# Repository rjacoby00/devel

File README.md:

# Devel
### Ryan Jacoby

This is a repository full of random bits of code I have written for various assingments, projects, and classes over time.  Some of the code I am not allowed to share and has been omited due to it being private, a homework solution, copyrighted code that I cannot distribute, or secret/classified information.  If you have any questions or need to see something that you think might have been redacted, feel free to email me at [rjacoby00@icloud.com](mailto:rjacoby00@icloud.com).

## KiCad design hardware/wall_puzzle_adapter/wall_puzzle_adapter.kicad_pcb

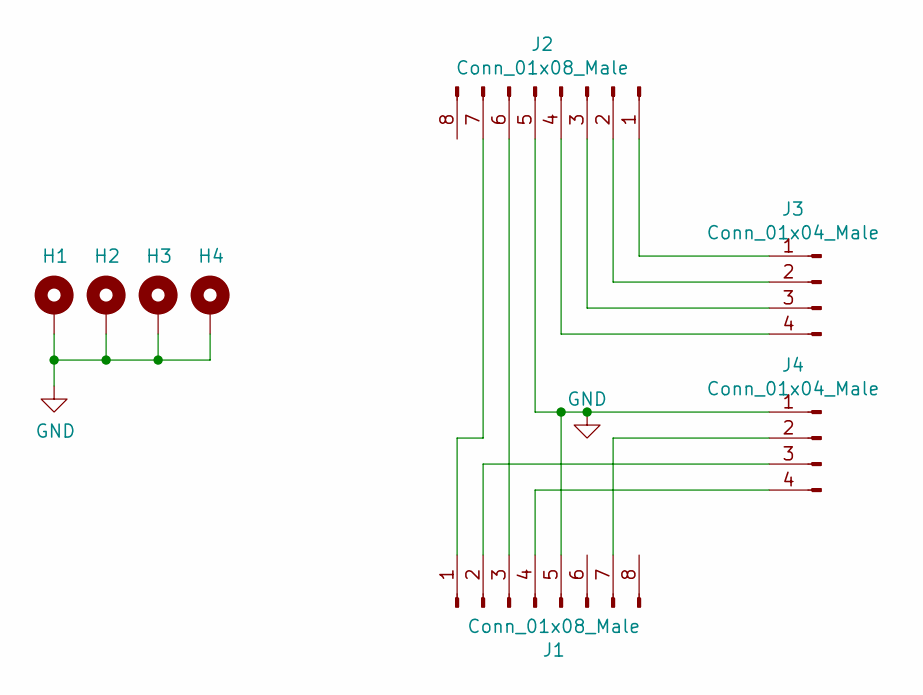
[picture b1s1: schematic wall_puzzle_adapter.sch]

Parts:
H1, H2, H3, H4: MountingHole_Pad; MountingHole_4mm_Pad_Via
J1: Conn_01x08_Male; RJ45_Amphenol_54602-x08_Horizontal
J2: Conn_01x08_Male; JST_XH_S8B-XH-A_1x08_P2.50mm_Horizontal
J3, J4: Conn_01x04_Male; TerminalBlock_Altech_AK300-4_P5.00mm

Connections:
GND: H1.1, H2.1, H3.1, H4.1, J1.5, J2.5, J4.1
unnamed: J1.1, J2.7
unnamed: J1.2, J4.3
unnamed: J1.3, J2.6
unnamed: J1.4, J4.4
unnamed: J1.7, J4.2
unnamed: J2.1, J3.1
unnamed: J2.2, J3.2
unnamed: J2.3, J3.3
unnamed: J2.4, J3.4

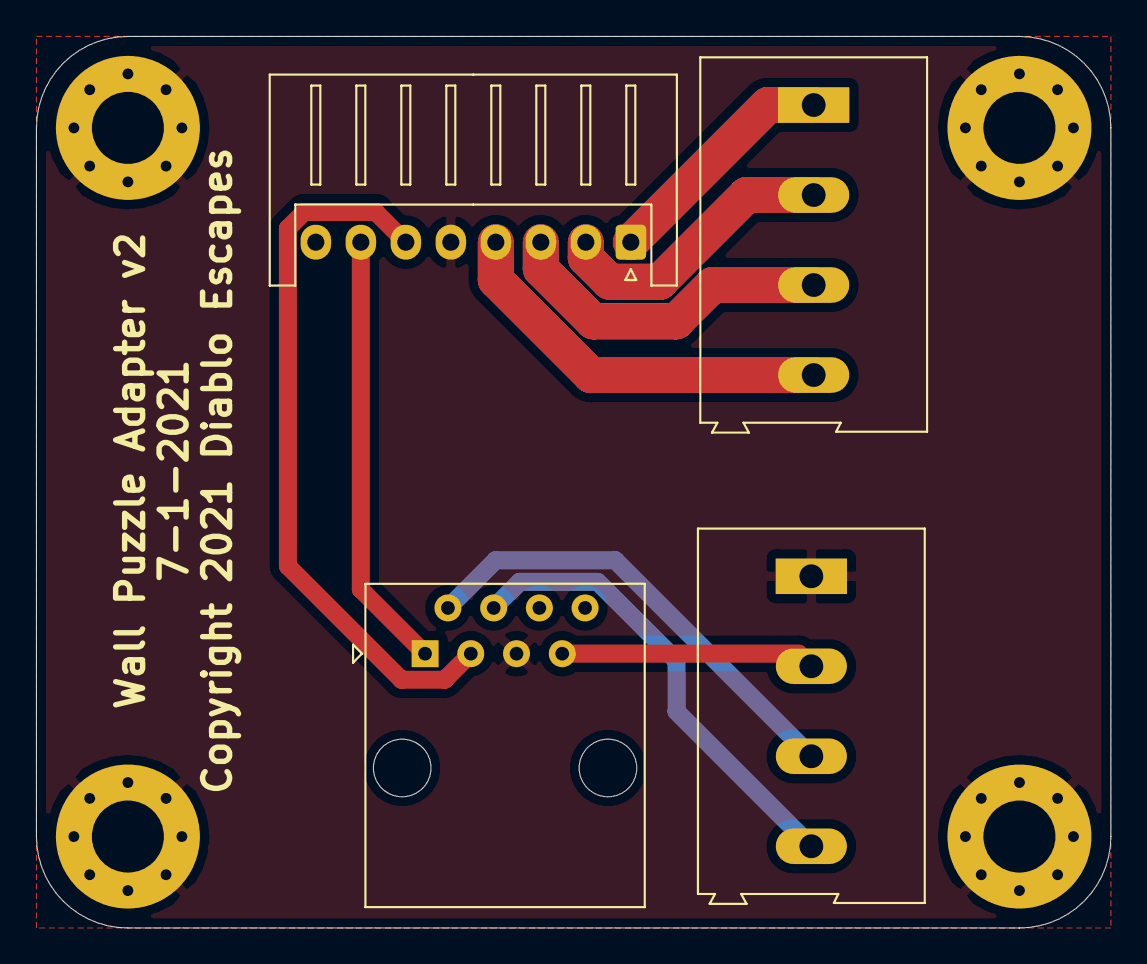
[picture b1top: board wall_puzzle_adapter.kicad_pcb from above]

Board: 2 copper layers, 59.7 x 49.5 mm, 8 parts (0 on the bottom side), 10 nets.

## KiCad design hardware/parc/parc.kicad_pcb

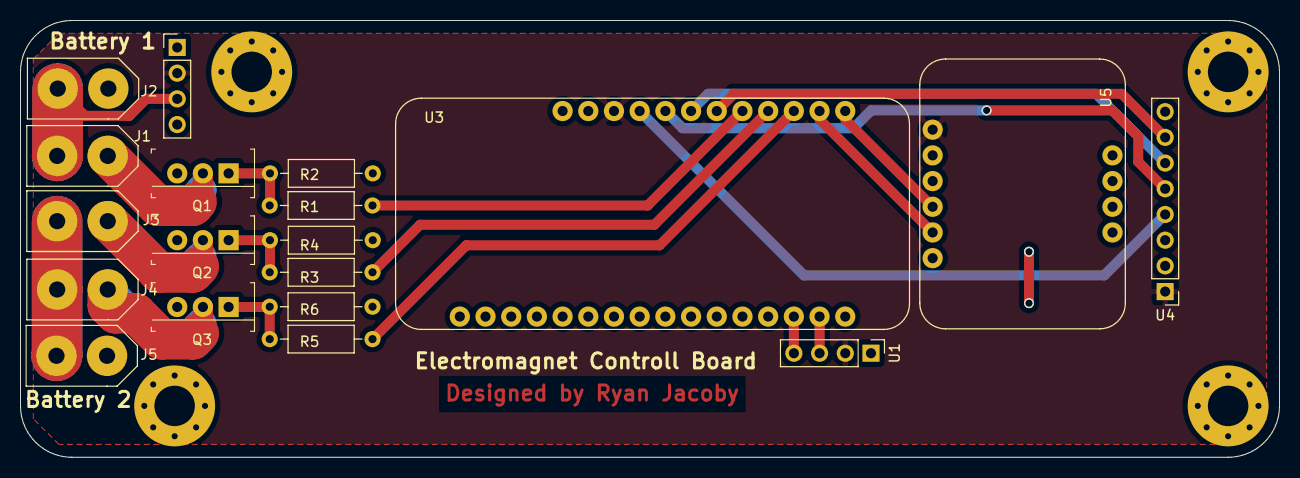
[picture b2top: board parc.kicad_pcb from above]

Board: 2 copper layers, 124.5 x 43.2 mm, 23 parts (0 on the bottom side), 21 nets.

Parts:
H1, H2, H3, H4: MountingHole_Pad; MountingHole_4mm_Pad_Via
J1, J2, J3, J4, J5: XT30
Q1, Q2, Q3: IRLB3034PBF; TO-220-3
R1, R3, R5: 1K; R_Axial_DIN0207_L6.3mm_D2.5mm_P10.16mm_Horizontal
R2, R4, R6: 1M; R_Axial_DIN0207_L6.3mm_D2.5mm_P10.16mm_Horizontal
U1: HC06; PinHeader_1x04_P2.54mm_Vertical
U2: MPM3610; PinHeader_1x04_P2.54mm_Vertical
U3: FeatherAdaloggerM0; Feather
U4: BMP388_Breakout; PinHeader_1x08_P2.54mm_Vertical
U5: BNO055_Breakout

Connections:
+5V: U1.2, U2.2, U3.19, U4.1, U5.1
B1: J1.2, J2.2, U2.3
B2: J3.2, J4.2, J5.2
GND: H1.1, H2.1, H3.1, H4.1, J2.1, J5.1, Q1.3, Q2.3, Q3.3, R2.2, R4.2, R6.2, U1.1, U2.1, U3.4, U3.16, U4.3, U5.3
M1: R1.1, U3.24
M2: R3.1, U3.25
M3: R5.1, U3.26
unnamed: J1.1, Q1.2
unnamed: J3.1, Q2.2
unnamed: J4.1, Q3.2
unnamed: Q1.1, R1.2, R2.1
unnamed: Q2.1, R3.2, R4.1
unnamed: Q3.1, R5.2, R6.1
unnamed: U1.3, U3.15
unnamed: U1.4, U3.14
unnamed: U3.20, U4.4
unnamed: U3.21, U4.5
unnamed: U3.22, U4.6
unnamed: U3.23, U4.7
unnamed: U3.27, U5.5
unnamed: U3.28, U5.4

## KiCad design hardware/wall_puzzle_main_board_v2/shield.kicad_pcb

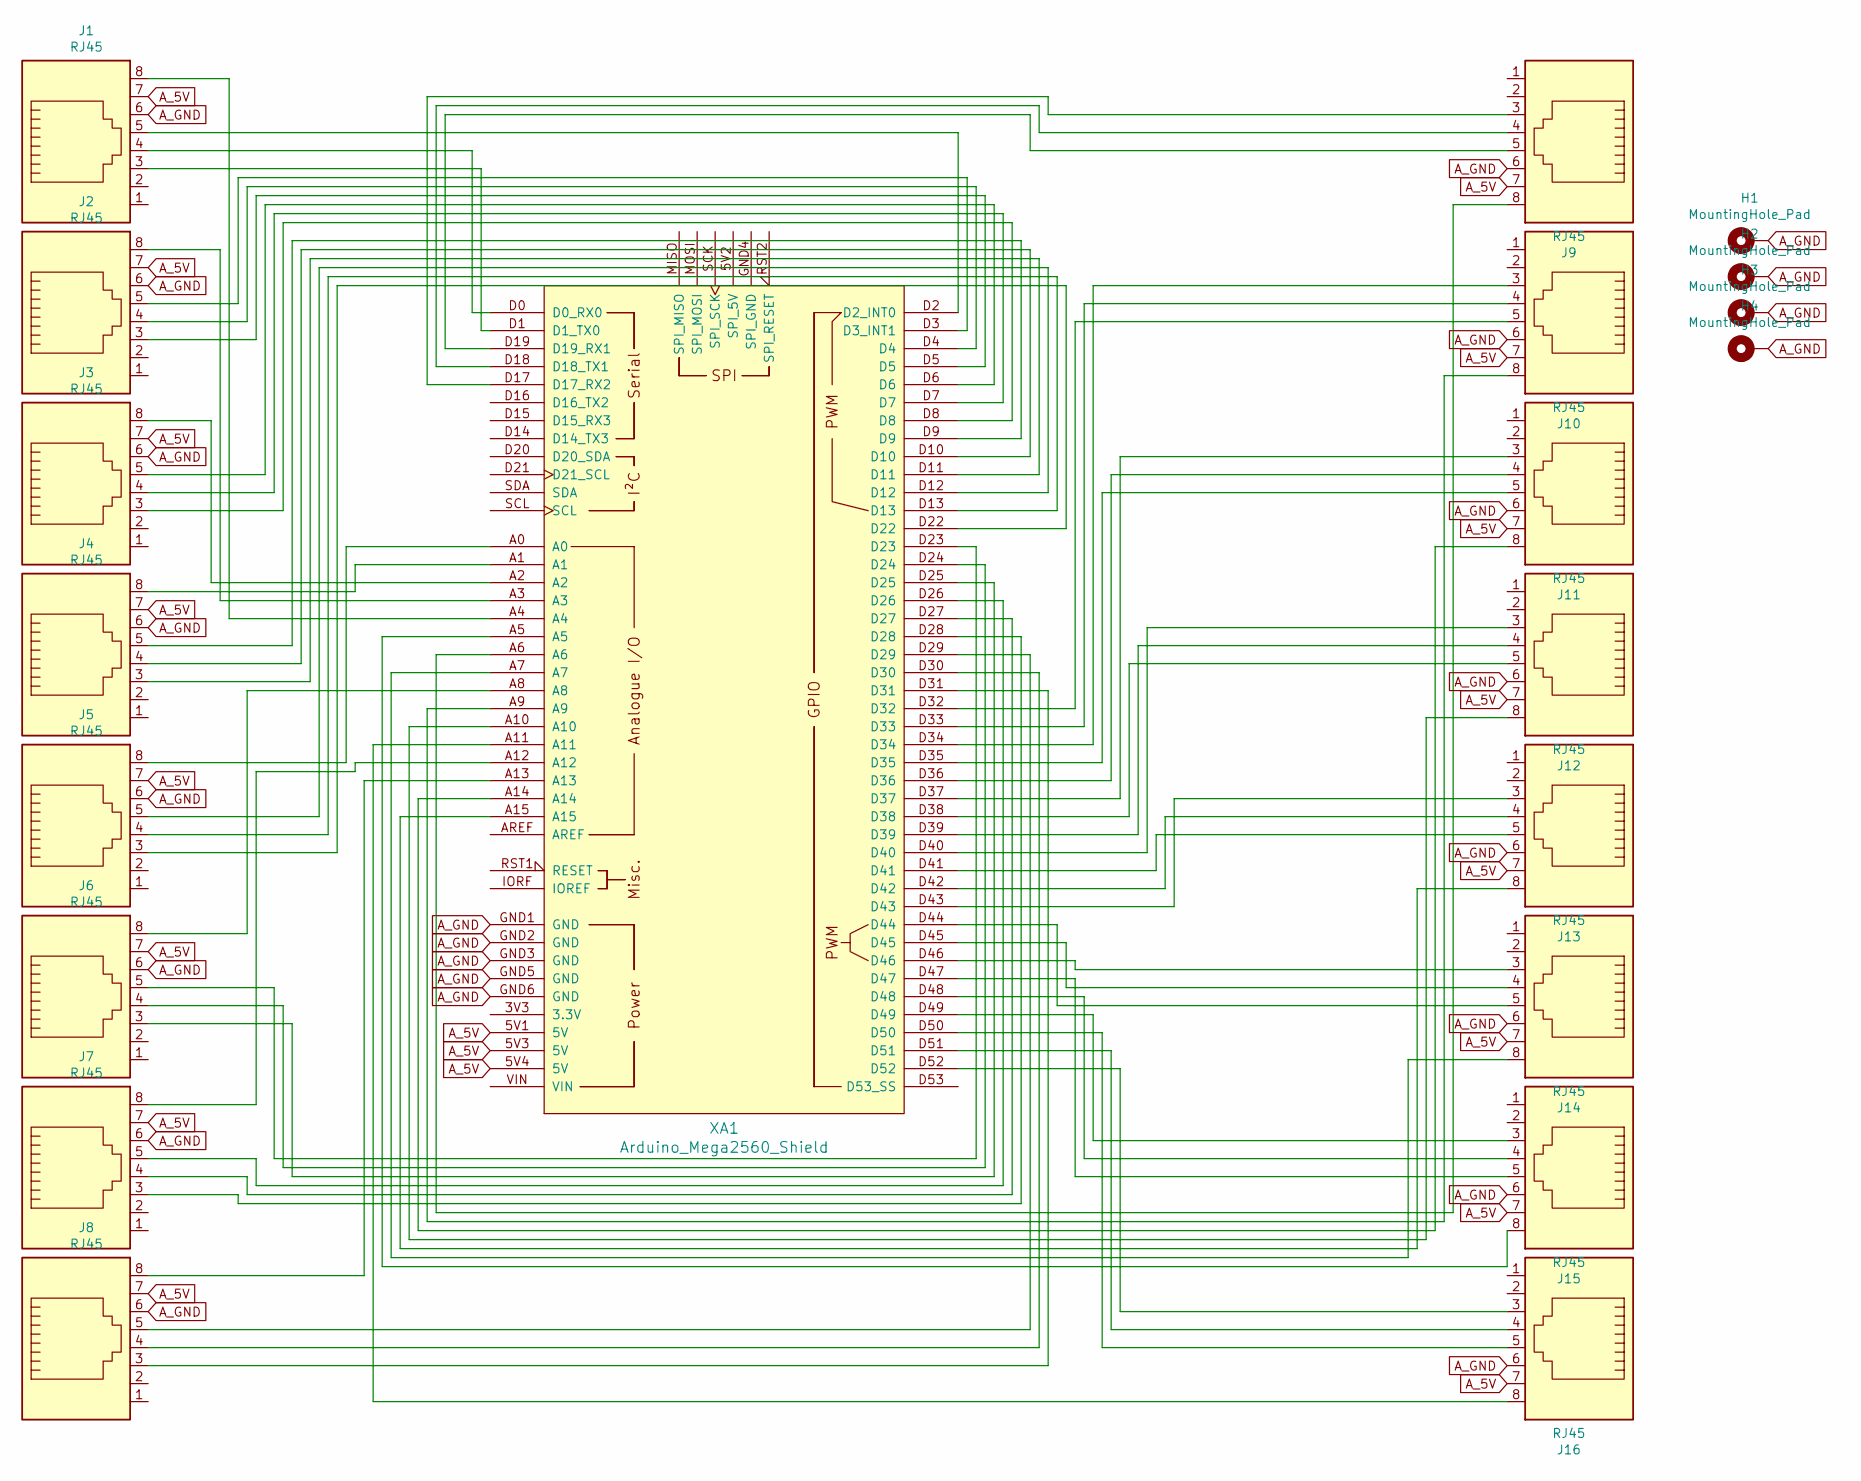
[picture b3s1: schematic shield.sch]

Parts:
H1, H2, H3, H4: MountingHole_Pad; MountingHole_3.2mm_M3_Pad_Via
J1, J2, J3, J4, J5, J6, J7, J8, J9, J10, J11, J12, J13, J14, J15, J16: RJ45; RJ45_PJ012
XA1: Arduino_Mega2560_Shield

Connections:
A_5V: J1.7, J2.7, J3.7, J4.7, J5.7, J6.7, J7.7, J8.7, J9.7, J10.7, J11.7, J12.7, J13.7, J14.7, J15.7, J16.7, XA1.5V1 (5V), XA1.5V3 (5V), XA1.5V4 (5V)
A_GND: H1.1, H2.1, H3.1, H4.1, J1.6, J2.6, J3.6, J4.6, J5.6, J6.6, J7.6, J8.6, J9.6, J10.6, J11.6, J12.6, J13.6, J14.6, J15.6, J16.6, XA1.GND1 (GND), XA1.GND2 (GND), XA1.GND3 (GND), XA1.GND5 (GND), XA1.GND6 (GND)
unnamed: J1.3, XA1.D1 (D1_TX0)
unnamed: J1.4, XA1.D0 (D0_RX0)
unnamed: J1.5, XA1.D2 (D2_INT0)
unnamed: J1.8, XA1.A4
unnamed: J2.3, XA1.D5
unnamed: J2.4, XA1.D4
unnamed: J2.5, XA1.D3 (D3_INT1)
unnamed: J2.8, XA1.A3
unnamed: J3.3, XA1.D8
unnamed: J3.4, XA1.D7
unnamed: J3.5, XA1.D6
unnamed: J3.8, XA1.A2
unnamed: J4.3, XA1.D11
unnamed: J4.4, XA1.D10
unnamed: J4.5, XA1.D9
unnamed: J4.8, XA1.A1
unnamed: J5.3, XA1.D22
unnamed: J5.4, XA1.D13
unnamed: J5.5, XA1.D12
unnamed: J5.8, XA1.A0
unnamed: J6.3, XA1.D25
unnamed: J6.4, XA1.D24
unnamed: J6.5, XA1.D23
unnamed: J6.8, XA1.A8
unnamed: J7.3, XA1.D28
unnamed: J7.4, XA1.D27
unnamed: J7.5, XA1.D26
unnamed: J7.8, XA1.A12
unnamed: J8.3, XA1.D31
unnamed: J8.4, XA1.D30
unnamed: J8.5, XA1.D29
unnamed: J8.8, XA1.A13
unnamed: J9.3, XA1.D17 (D17_RX2)
unnamed: J9.4, XA1.D18 (D18_TX1)
unnamed: J9.5, XA1.D19 (D19_RX1)
unnamed: J9.8, XA1.A6
unnamed: J10.3, XA1.D34
unnamed: J10.4, XA1.D33
unnamed: J10.5, XA1.D32
unnamed: J10.8, XA1.A9
unnamed: J11.3, XA1.D37
unnamed: J11.4, XA1.D36
unnamed: J11.5, XA1.D35
unnamed: J11.8, XA1.A14
unnamed: J12.3, XA1.D40
unnamed: J12.4, XA1.D39
unnamed: J12.5, XA1.D38
unnamed: J12.8, XA1.A10
unnamed: J13.3, XA1.D43
unnamed: J13.4, XA1.D42
unnamed: J13.5, XA1.D41
unnamed: J13.8, XA1.A15
unnamed: J14.3, XA1.D46
unnamed: J14.4, XA1.D45
unnamed: J14.5, XA1.D44
unnamed: J14.8, XA1.A7
unnamed: J15.3, XA1.D49
unnamed: J15.4, XA1.D48
unnamed: J15.5, XA1.D47
unnamed: J15.8, XA1.A5
unnamed: J16.3, XA1.D52
unnamed: J16.4, XA1.D51
unnamed: J16.5, XA1.D50
unnamed: J16.8, XA1.A11

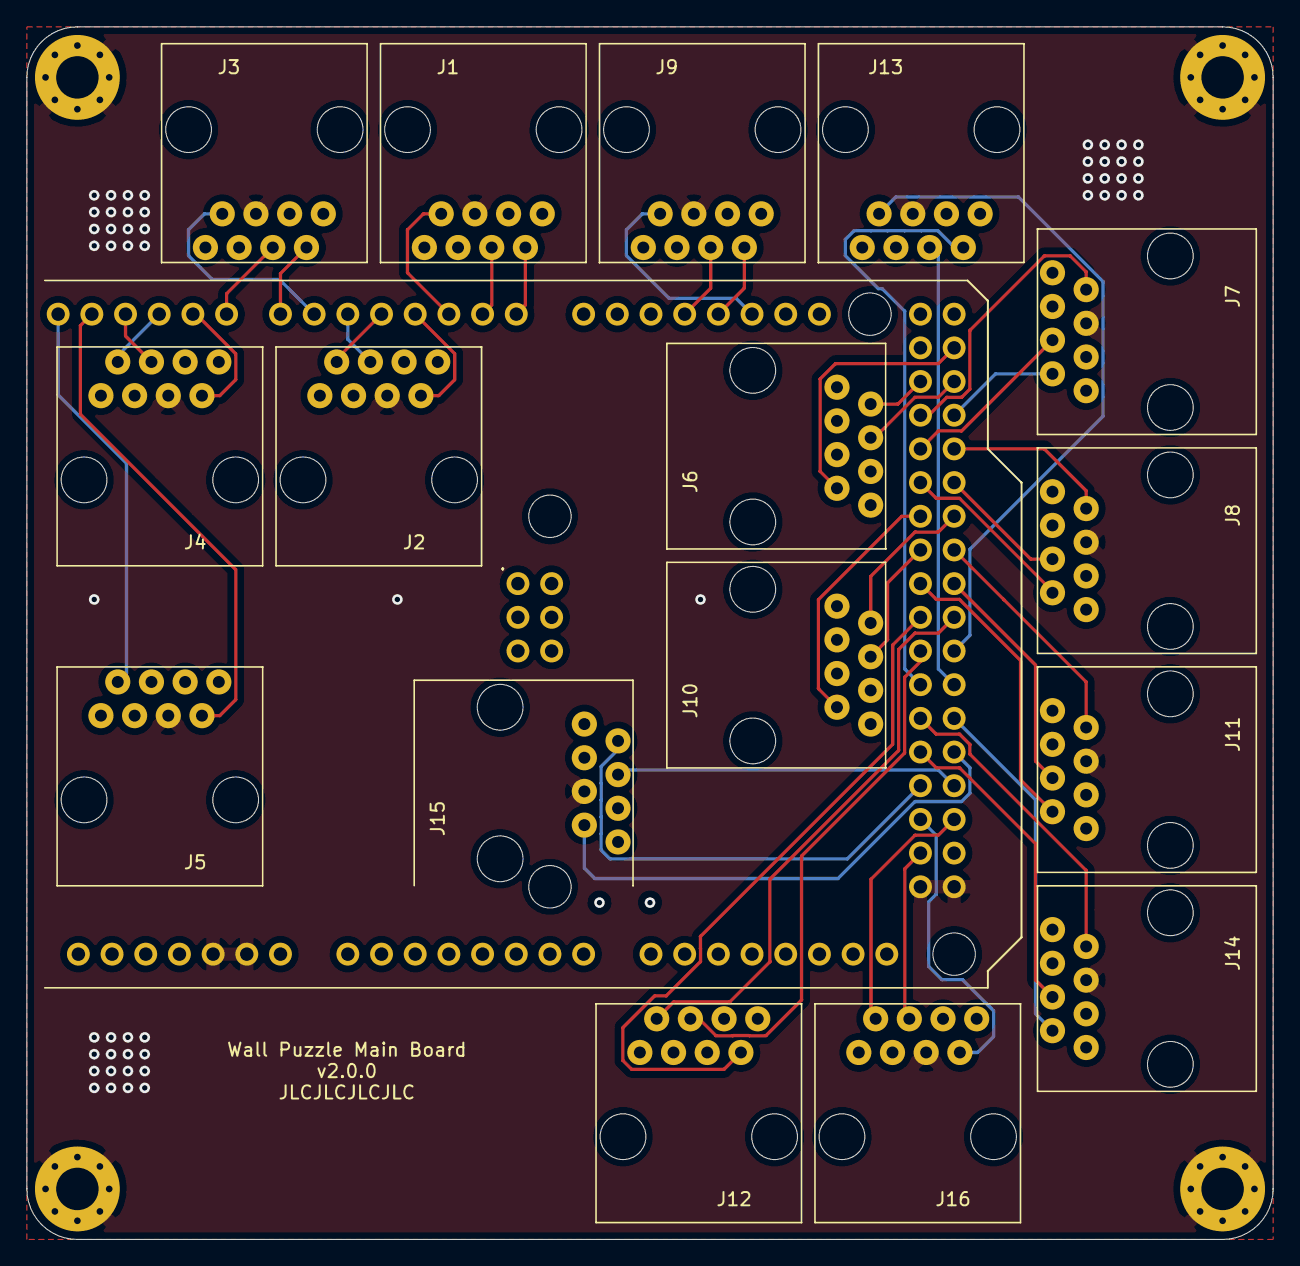
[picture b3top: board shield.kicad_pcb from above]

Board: 4 copper layers, 94.0 x 91.4 mm, 21 parts (0 on the bottom side), 66 nets.

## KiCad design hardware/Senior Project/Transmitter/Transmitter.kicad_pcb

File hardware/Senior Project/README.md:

# High School Senior Project

This is the circuit and PCB design for my Senior Research Project.  My project was to research the future economic impacts of the Internet of Things on manufacturing and to design a simple IoT board.  This is a small temperature sensor board that transmits it's data over LoRa.  The board is untested as the parts I orignally designed it for were out of stock by the time it was complete due to the global chip shortage in 2021.  The firmware is mostly just the template files generated for my hardware configuration by STM32CubeIDE.  I've stripped out most of the project files from that with a gitignore.

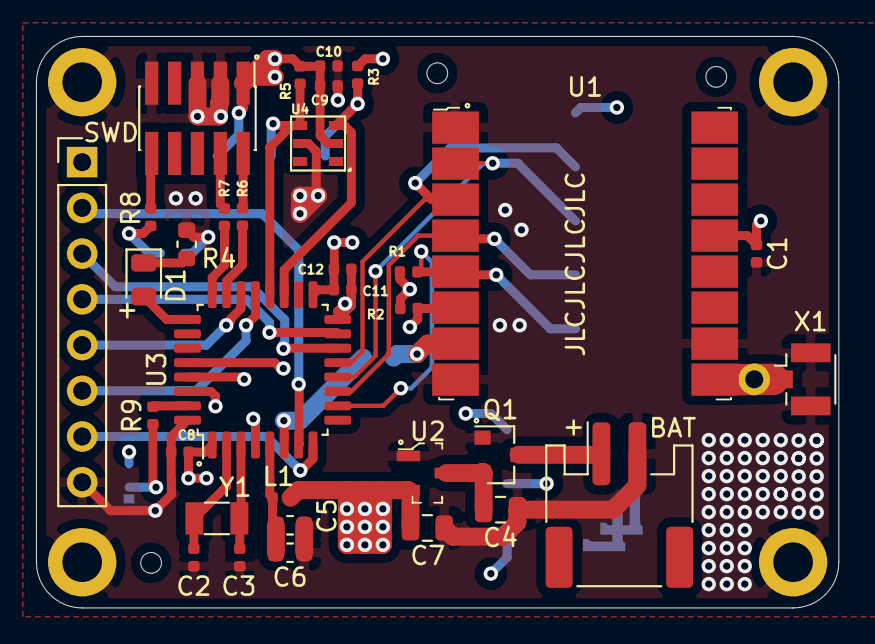
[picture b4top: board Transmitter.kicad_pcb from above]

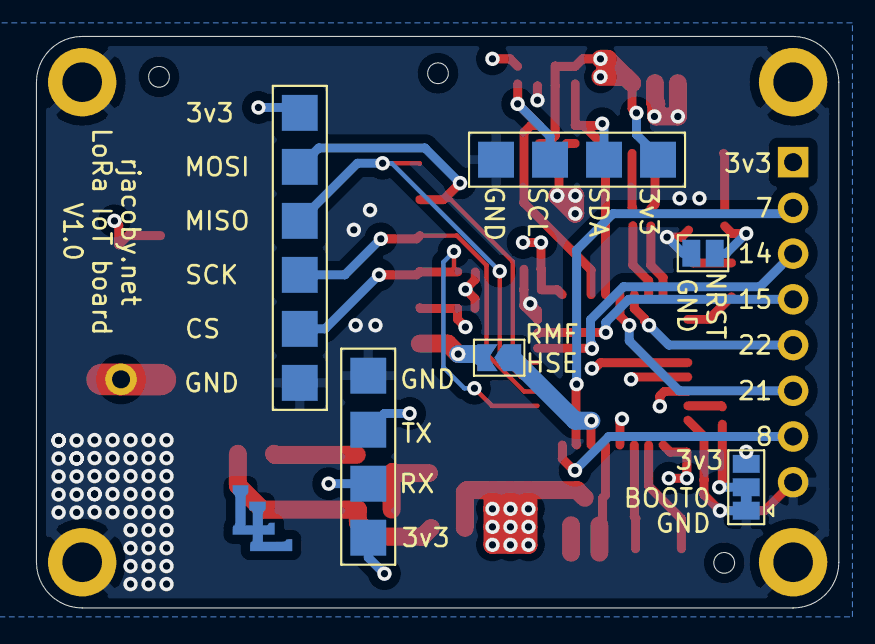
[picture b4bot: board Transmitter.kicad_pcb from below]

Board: 4 copper layers, 44.6 x 31.8 mm, 44 parts (6 on the bottom side), 35 nets.

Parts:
C1, C10, C12: 10u; C_0402_1005Metric
C2, C3: 12p; C_0402_1005Metric
C4, C7: 1u; C_0805_2012Metric
C5: 1u; C_0603_1608Metric
C6: 10n; C_0603_1608Metric
C8, C9, C11: 100n; C_0402_1005Metric
CFG1: 0; SolderJumper-2_P1.3mm_Open_TrianglePad1.0x1.5mm
D1: Blue; LED_0805_2012Metric
H1, H2, H3, H4: MountingHole_Pad; MountingHole_2.2mm_M2_DIN965_Pad
J1: Conn_01x01_Male; Wire_Antena
J2: Bat; JST_PH_S2B-PH-SM4-TB_1x02-1MP_P2.00mm_Horizontal
J3: UART; TestPoint_SMD_4Pads_2mm
J4: SWD; PinHeader_2x05_P1.27mm_Vertical_SMD
J5: I2C; TestPoint_SMD_4Pads_2mm
J6: SPI; TestPoint_SMD_6Pads_2mm
J7: GPIO; PinHeader_1x08_P2.54mm_Vertical
L1: 39n; L_0402_1005Metric
Q1: AO3401A; SOT-23
R1, R2: 100K; R_0402_1005Metric
R3, R5, R9: 10k; R_0402_1005Metric
R4: 1k5; R_0603_1608Metric
R6, R7, R8: 22; R_0402_1005Metric
S1: SW_SPDT; SolderJumper-3_P1.3mm_Bridged12_Pad1.0x1.5mm
S2: GPTS203211B; SolderJumper-2_P1.3mm_Open_Pad1.0x1.5mm
U1: RFM69HCW; RF_Module_COM-13909
U2: XC6206P332MR; SOT-23-3
U3: STM32L010K4T6; LQFP-32_7x7mm_P0.8mm
U4: AHT20; LGA-6_3x3mm_AHT20
X1: UFL_SMA; U.FL_Hirose_U.FL-R-SMT-1_Vertical
Y1: 32.768k; Crystal_SMD_3215-2Pin_3.2x1.5mm

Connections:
+3.3VA: C5.1, C6.1, L1.2, U3.5
+3V3: C1.1, C7.1, C8.1, C9.1, C10.1, C11.1, C12.1, J3.1, J4.1, J5.1, J6.1, J7.1, L1.1, R1.2, R2.2, R3.2, R5.2, S1.3, U1.13, U2.2, U3.1, U3.17, U4.2
ADC_1: J7.2, U3.7
ADC_8: J7.3, U3.14
ADC_9: J7.4, U3.15
BOOT0: R9.2, U3.31
CS: J6.5, R1.1, U1.5, U3.10
GND: C1.2, C2.2, C3.2, C4.2, C5.2, C6.2, C7.2, C8.2, C9.2, C10.2, C11.2, C12.2, H1.1, H2.1, H3.1, H4.1, J2.2, J3.4, J4.3, J4.5, J4.9, J5.4, J6.6, J7.8, Q1.1, R4.1, S1.1, S2.2, U1.1, U1.8, U1.10, U2.1, U3.16, U3.32, U4.5, X1.2
HSE_IN: CFG1.1, U3.6
I2C_SCL: J5.3, R3.1, U3.19, U4.3
I2C_SDA: J5.2, R5.1, U3.20, U4.4
MISO: J6.3, U1.2, U3.12
MOSI: J6.2, U1.3, U3.13
NRST: R8.1, S2.1, U3.4
unnamed: C4.1, Q1.2, U2.3
unnamed: CFG1.2, U1.7
unnamed: D1.1, R4.2
unnamed: D1.2, U3.25
unnamed: J1.1, U1.9, X1.1
unnamed: J4.2, R6.2
unnamed: J4.4, R7.2
unnamed: J4.10, R8.2
unnamed: R9.1, S1.2
OSC_IN: C2.1, U3.2, Y1.1
OSC_OUT: C3.1, U3.3, Y1.2
RST: R2.1, U1.6, U3.28
SCK: J6.4, U1.4, U3.11
SWCLK: R7.1, U3.24
SWDIO: R6.1, U3.23
SYS_WAKEUP: J7.7, U3.8
USART2_CTS: J7.6, U3.21
USART2_RTS: J7.5, U3.22
USART2_RX: J3.2, U3.30
USART2_TX: J3.3, U3.29
VIN: J2.1, Q1.3

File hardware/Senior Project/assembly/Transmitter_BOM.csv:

Comment,Designator,Footprint,LCSC Part #
10u Unpolarized capacitor,"C1,C10,C12",C_0402_1005Metric, C15525
12p Unpolarized capacitor,"C2,C3",C_0402_1005Metric, C1547
1u Unpolarized capacitor,"C4,C7",C_0805_2012Metric, C28323
1u Unpolarized capacitor,C5,C_0603_1608Metric, C15849
10n Unpolarized capacitor,C6,C_0603_1608Metric, C57112
100n Unpolarized capacitor,"C8,C9,C11",C_0402_1005Metric, C1525
Blue Light emitting diode,D1,LED_0805_2012Metric, C2293
39n Inductor,L1,L_0402_1005Metric, C86063
"AO3401A -4.0A Id, -30V Vds, P-Channel MOSFET, SOT-23",Q1,SOT-23, C15127
100K Resistor,"R1,R2",R_0402_1005Metric, C25741
10k Resistor,"R3,R5,R9",R_0402_1005Metric, C25744
1k5 Resistor,R4,R_0603_1608Metric, C22843
22 Resistor,"R6,R7,R8",R_0402_1005Metric, C25092
"XC6206P332MR Positive 60-250mA Low Dropout Regulator, Fixed Output, SOT-23",U2,SOT-23-3,C5446
UFL_SMA ,X1,U.FL_Hirose_U.FL-R-SMT-1_Vertical, C88374
32.768k Two pin crystal,Y1,Crystal_SMD_3215-2Pin_3.2x1.5mm, C32346

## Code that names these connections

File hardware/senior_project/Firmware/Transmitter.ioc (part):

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Mcu.Name=STM32L010K4Tx
Mcu.Package=LQFP32
Mcu.UserName=STM32L010K4Tx
PA0-CK_IN.Mode=HSE-External-Clock-Source-for-TinyNemo
PA0-CK_IN.Signal=RCC_CK_IN
PA1.Mode=IN1
PA1.Signal=ADC_IN1
PA10.Mode=I2C
PA10.Signal=I2C1_SDA
PA11.Mode=CTS_RTS
PA11.Signal=USART2_CTS
PA12.Mode=CTS_RTS
PA12.Signal=USART2_RTS
PA13.Mode=Serial_Wire
PA13.Signal=SYS_SWDIO
PA14.Mode=Serial_Wire
PA14.Signal=SYS_SWCLK
PA15.Signal=GPIO_Output
PA2.Mode=SYS_WakeUp2
PA2.Signal=SYS_WKUP3
PA3.Mode=IN3
PA3.Signal=ADC_IN3
PA4.Mode=NSS_Signal_Hard_Output
PA4.Signal=SPI1_NSS
PA5.Mode=Full_Duplex_Master
PA5.Signal=SPI1_SCK
PA6.Mode=Full_Duplex_Master
PA6.Signal=SPI1_MISO
PA7.Mode=Full_Duplex_Master
PA7.Signal=SPI1_MOSI
PA9.Mode=I2C
PA9.Signal=I2C1_SCL
PB0.Mode=IN8
PB0.Signal=ADC_IN8
PB1.Mode=IN9
PB1.Signal=ADC_IN9
PB6.Mode=Asynchronous
PB6.Signal=USART2_TX
PB7.Mode=Asynchronous
PB7.Signal=USART2_RX
PC14-OSC32_IN.Mode=LSE-External-Oscillator
PC14-OSC32_IN.Signal=RCC_OSC32_IN
PC15-OSC32_OUT.Mode=LSE-External-Oscillator
PC15-OSC32_OUT.Signal=RCC_OSC32_OUT
RCC.HSE_VALUE=8000000
RCC.SYSCLKFreq_VALUE=2097000
board=custom

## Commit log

2020-07-16 Re-inital commit. Hopefully there aren't any sesitive / classified files this time.
2020-07-18 Complete Module 9 in COMSC-165
2020-07-20 Add some READMEs before making repo public
2021-07-01 Large update containing new work and redacted files from COMSC200 and COMSC210
2021-07-02 Add hardware project
2021-07-02 Remove .lib files from gitignore; they're important and used by KiCad
2021-07-03 Work on lattice board
2021-07-04 Work on lattice board; add TODO list to lattice board

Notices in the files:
hardware/wall_puzzle_adapter/wall_puzzle_adapter.kicad_pcb:
Copyright 2021 Diablo Escapes
